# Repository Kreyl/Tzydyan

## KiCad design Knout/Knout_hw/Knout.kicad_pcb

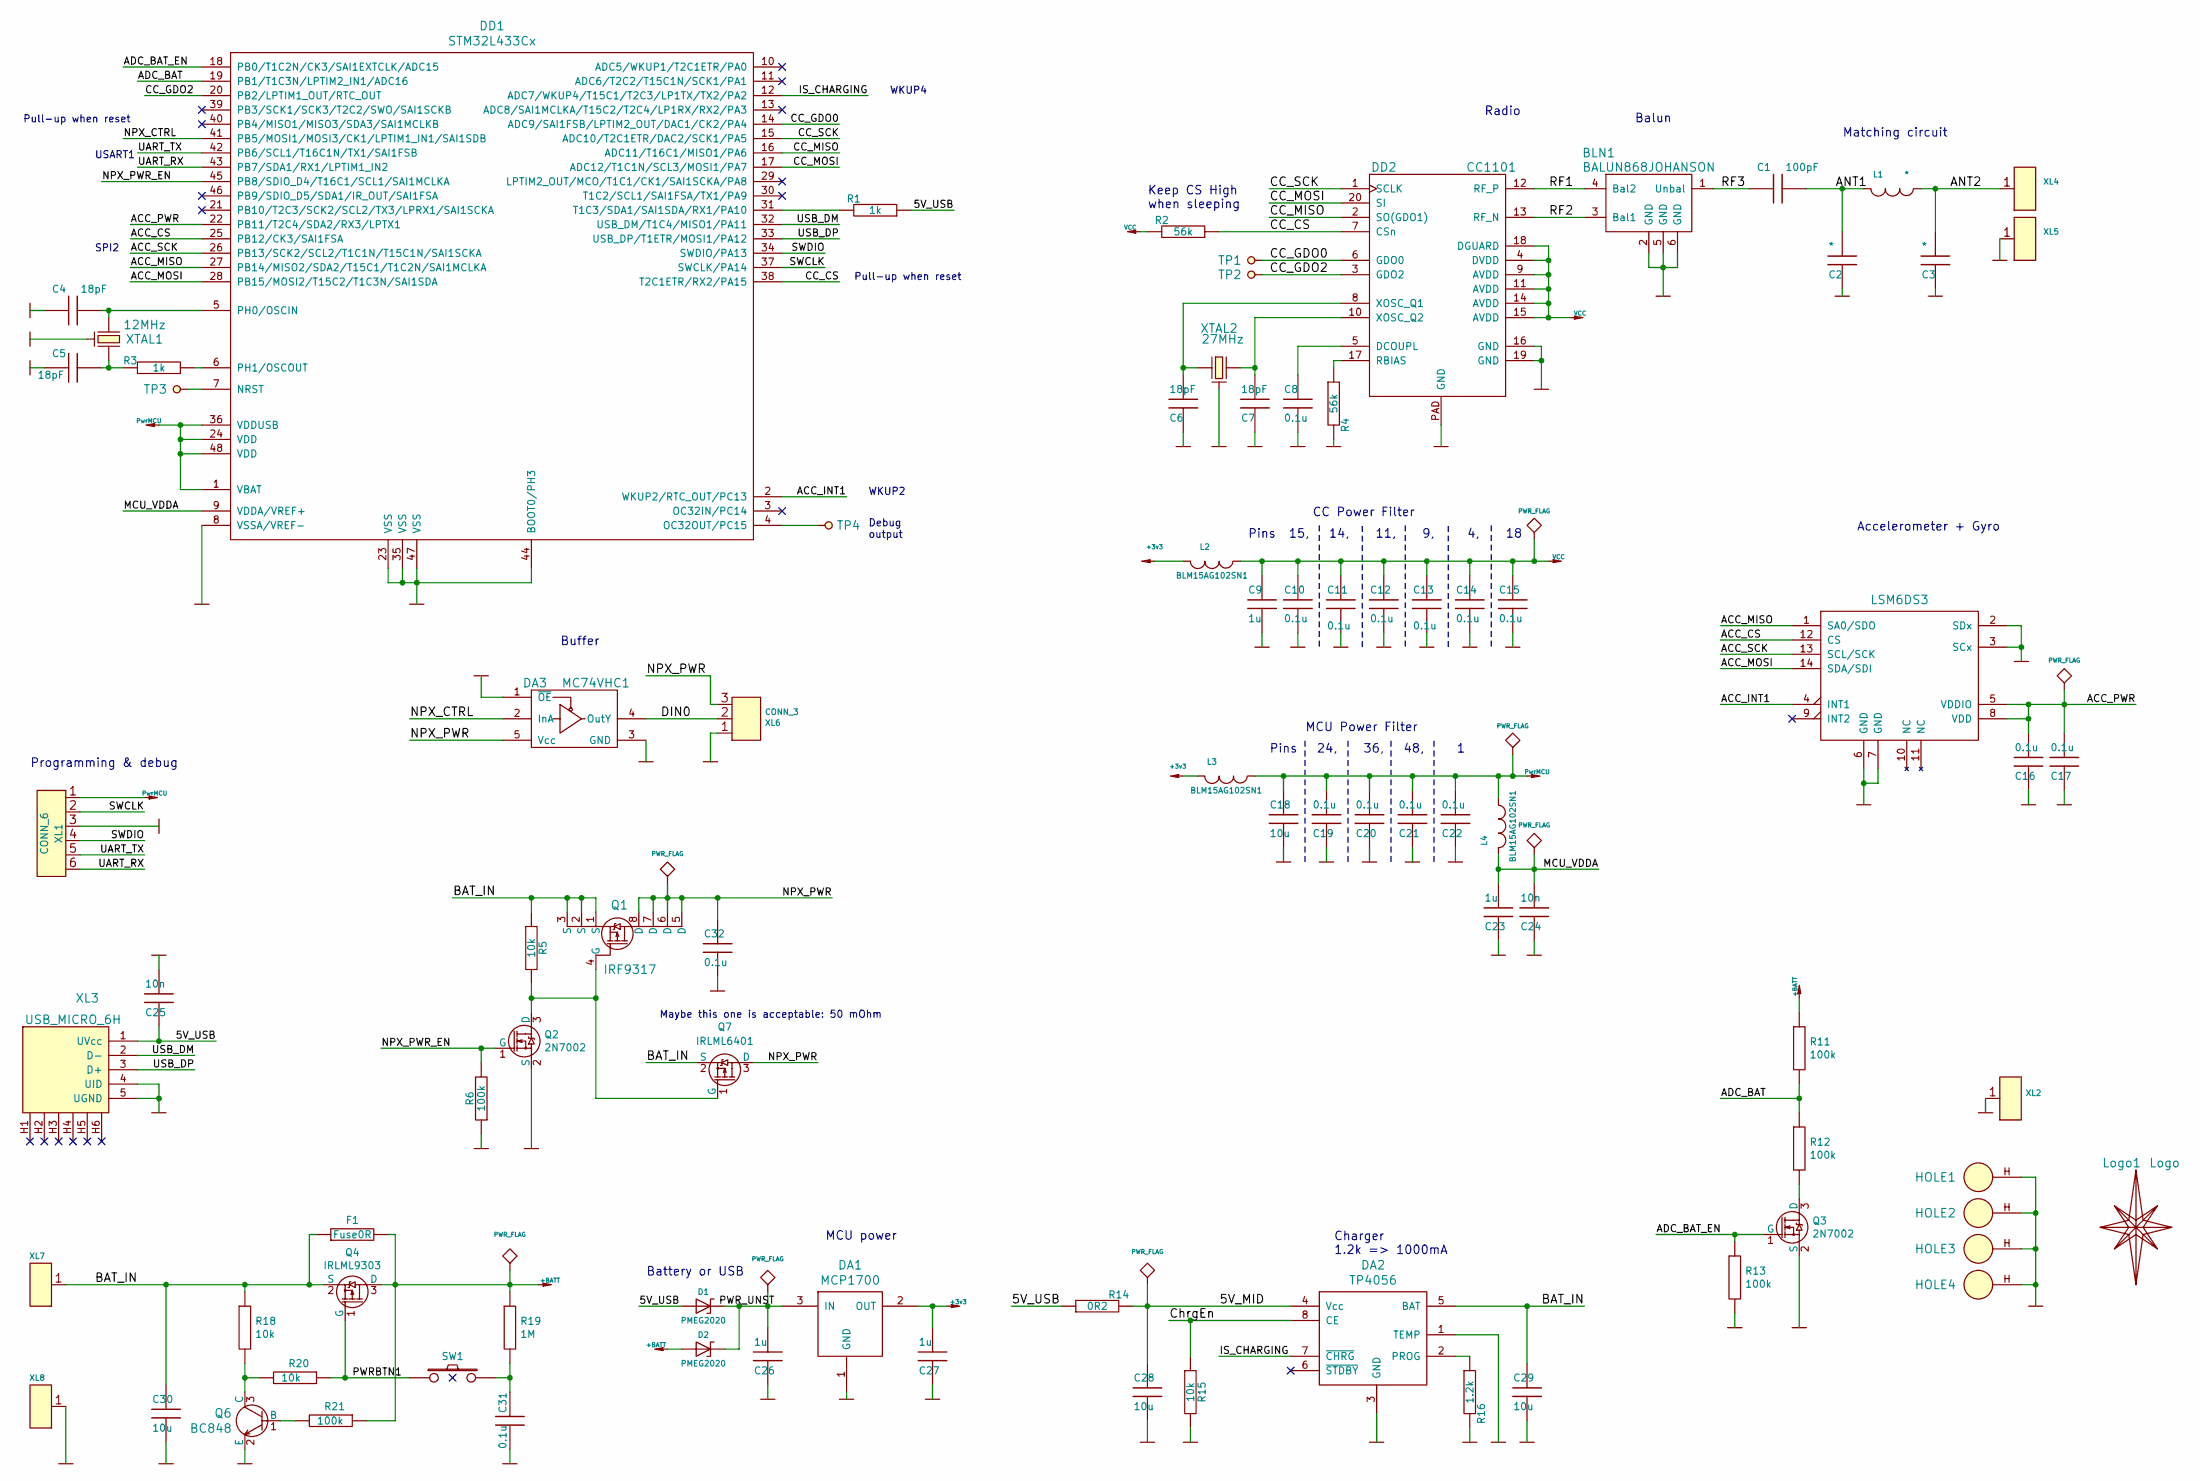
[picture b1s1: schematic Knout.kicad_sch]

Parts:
BLN1: BALUN868JOHANSON; BALUN_JOHANSON868
C1: 100pF; CAP_0402
C2, C3: *; CAP_0402
C4, C5, C6, C7: 18pF; CAP_0603_Silks
C8, C10, C11, C12, C13, C14, C15, C16, C17, C19, C20, C21, C22, C31, C32: 0.1u; CAP_0603_Silks
C9, C23, C26, C27: 1u; CAP_0603_Silks
C18, C28, C29, C30: 10u; CAP_0603_Silks
C24, C25: 10n; CAP_0603_Silks
D1, D2: PMEG2020; SOD323
DA1: MCP1700; SOT23-3A
DA2: TP4056; SO8_150MIL
DA3: MC74VHC1; SOT23-5
DD1: STM32L433Cx; LQFP48
DD2: CC1101; QFN20
DD3: LSM6DS3; 14_3x2d5_p0d5
F1: Fuse0R; RES_0603_FUSE
HOLE1, HOLE2, HOLE3, HOLE4: HOLE_METALLED; Hole2d2_out3d5mm
L1: *; IND_0402
L2, L3, L4: BLM15AG102SN1; IND_0402
Logo1: Logo; Ostranna_8x8
Q1: IRF9317; SO8_150MIL
Q2, Q3: 2N7002; SOT23-3
Q4: IRLML9303; SOT23-3
Q6: BC848; SOT23-3
Q7: IRLML6401; SOT23-3
R1, R3: 1k; RES_0603
R2, R4: 56k; RES_0603
R5, R15, R18, R20: 10k; RES_0603
R6, R11, R12, R13, R21: 100k; RES_0603
R14: 0R2; RES_1206
R16: 1.2k; RES_0603
R19: 1M; RES_0603
SW1: BUTTON_H; BTN_IT1198
TP1, TP2, TP3, TP4: TESTPOINT; TESTPOINT_1MM
XL1: CONN_6; PLS-6
XL2, XL7: CONN_1; PLS-1Rnd
XL3: USB_MICRO_6H; USBmicro_MOLEX_1050170001
XL4, XL5, XL8: CONN_1; PLS-1Square
XL6: CONN_3; SLD_3_2D5
XTAL1: 12MHz; 03225C4
XTAL2: 27MHz; 03225C4

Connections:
+3v3: C27.1, DA1.2 (OUT), L2.2, L3.2
+BATT: D2.A, F1.2, Q4.3 (D), R11.1, R19.1, R21.1
/5V_MID: C28.2, DA2.4 (Vcc), R14.2
/5V_USB: C25.2, D1.A, R1.1, R14.1, XL3.1 (UVcc)
/ACC_CS: DD1.25 (PB12/CK3/SAI1FSA), DD3.12 (CS)
/ACC_INT1: DD1.2 (WKUP2/RTC_OUT/PC13), DD3.4 (INT1)
/ACC_MISO: DD1.27 (PB14/MISO2/SDA2/T15C1/T1C2N/SAI1MCLKA), DD3.1 (SA0/SDO)
/ACC_MOSI: DD1.28 (PB15/MOSI2/T15C2/T1C3N/SAI1SDA), DD3.14 (SDA/SDI)
/ACC_PWR: C16.1, C17.1, DD1.22 (PB11/T2C4/SDA2/RX3/LPTX1), DD3.5 (VDDIO), DD3.8 (VDD)
/ACC_SCK: DD1.26 (PB13/SCK2/SCL2/T1C1N/T15C1N/SAI1SCKA), DD3.13 (SCL/SCK)
/ADC_BAT: DD1.19 (PB1/T1C3N/LPTIM2_IN1/ADC16), R11.2, R12.1
/ADC_BAT_EN: DD1.18 (PB0/T1C2N/CK3/SAI1EXTCLK/ADC15), Q3.1 (G), R13.1
/ANT1: C1.1, C2.1, L1.2
/ANT2: C3.1, L1.1, XL4.1
/BAT_IN: C29.2, C30.2, DA2.5 (BAT), F1.1, Q1.1 (S), Q1.2 (S), Q1.3 (S), Q4.2 (S), Q7.2 (S), R5.1, R18.1, XL7.1
/CC_CS: DD1.38 (T2C1ETR/RX2/PA15), DD2.7 (CSn), R2.1
/CC_GDO0: DD1.14 (ADC9/SAI1FSB/LPTIM2_OUT/DAC1/CK2/PA4), DD2.6 (GDO0), TP1.1
/CC_GDO2: DD1.20 (PB2/LPTIM1_OUT/RTC_OUT), DD2.3 (GDO2), TP2.1
/CC_MISO: DD1.16 (ADC11/T16C1/MISO1/PA6), DD2.2 (SO(GDO1))
/CC_MOSI: DD1.17 (ADC12/T1C1N/SCL3/MOSI1/PA7), DD2.20 (SI)
/CC_SCK: DD1.15 (ADC10/T2C1ETR/DAC2/SCK1/PA5), DD2.1 (SCLK)
/ChrgEn: DA2.8 (CE), R15.1
/DIN0: DA3.4 (OutY), XL6.2 (PM)
/IS_CHARGING: DA2.7 (~CHRG), DD1.12 (ADC7/WKUP4/T15C1/T2C3/LP1TX/TX2/PA2)
/MCU_VDDA: C23.1, C24.1, DD1.9 (VDDA/VREF+), L4.2
/NPX_CTRL: DA3.2 (InA), DD1.41 (PB5/MOSI1/MOSI3/CK1/LPTIM1_IN1/SAI1SDB)
/NPX_PWR: C32.2, DA3.5 (Vcc), Q1.5 (D), Q1.6 (D), Q1.7 (D), Q1.8 (D), Q7.3 (D), XL6.3
/NPX_PWR_EN: DD1.45 (PB8/SDIO_D4/T16C1/SCL1/SAI1MCLKA), Q2.1 (G), R6.2
/PWRBTN1: Q4.1 (G), R20.1, SW1.1
/PWR_UNST: C26.1, D1.C, D2.C, DA1.3 (IN)
/RF1: BLN1.4 (Bal2), DD2.12 (RF_P)
/RF2: BLN1.3 (Bal1), DD2.13 (RF_N)
/RF3: BLN1.1 (Unbal), C1.2
/SWCLK: DD1.37 (SWCLK/PA14), XL1.2
/SWDIO: DD1.34 (SWDIO/PA13), XL1.4
/UART_RX: DD1.43 (PB7/SDA1/RX1/LPTIM1_IN2), XL1.6
/UART_TX: DD1.42 (PB6/SCL1/T16C1N/TX1/SAI1FSB), XL1.5
/USB_DM: DD1.32 (USB_DM/T1C4/MISO1/PA11), XL3.2 (D-)
/USB_DP: DD1.33 (USB_DP/T1ETR/MOSI1/PA12), XL3.3 (D+)
GND: BLN1.2 (GND), BLN1.5 (GND), BLN1.6 (GND), C2.2, C3.2, C4.2, C5.2, C6.2, C7.2, C8.1, C9.2, C10.2, C11.2, C12.2, C13.2, C14.2, C15.2, C16.2, C17.2, C18.1, C19.2, C20.2, C21.2, C22.2, C23.2, C24.2, C25.1, C26.2, C27.2, C28.1, C29.1, C30.1, C31.2, C32.1, DA1.1 (GND), DA2.1 (TEMP), DA2.3 (GND), DA3.1 (~OE), DA3.3 (GND), DD1.8 (VSSA/VREF-), DD1.23 (VSS), DD1.35 (VSS), DD1.44 (BOOT0/PH3), DD1.47 (VSS), DD2.16 (GND), DD2.19 (GND), DD2.PAD (GND), DD3.2 (SDx), DD3.3 (SCx), DD3.6 (GND), DD3.7 (GND), HOLE1.H, HOLE2.H, HOLE3.H, HOLE4.H, Q2.2 (S), Q3.2 (S), Q6.2 (E), R4.2, R6.1, R13.2, R15.2, R16.2, XL1.3, XL2.1, XL3.4 (UID), XL3.5 (UGND), XL5.1, XL6.1, XL8.1, XTAL1.H, XTAL2.H
unnamed: C4.1, DD1.5 (PH0/OSCIN), XTAL1.1
unnamed: C5.1, R3.2, XTAL1.2
unnamed: C6.1, DD2.8 (XOSC_Q1), XTAL2.1
unnamed: C7.1, DD2.10 (XOSC_Q2), XTAL2.2
unnamed: C8.2, DD2.5 (DCOUPL)
unnamed: C31.1, R19.2, SW1.2
unnamed: DA2.2 (PROG), R16.1
unnamed: DD1.4 (OC32OUT/PC15), TP4.1
unnamed: DD1.6 (PH1/OSCOUT), R3.1
unnamed: DD1.7 (NRST), TP3.1
unnamed: DD1.31 (T1C3/SDA1/SAI1SDA/RX1/PA10), R1.2
unnamed: DD2.17 (RBIAS), R4.1
unnamed: Q1.4 (G), Q2.3 (D), Q7.1 (G), R5.2
unnamed: Q3.3 (D), R12.2
unnamed: Q6.1 (B), R21.2
unnamed: Q6.3 (C), R18.2, R20.2
PwrMCU: C18.2, C19.1, C20.1, C21.1, C22.1, DD1.1 (VBAT), DD1.24 (VDD), DD1.36 (VDDUSB), DD1.48 (VDD), L3.1, L4.1, XL1.1
VCC: C9.1, C10.1, C11.1, C12.1, C13.1, C14.1, C15.1, DD2.4 (DVDD), DD2.9 (AVDD), DD2.11 (AVDD), DD2.14 (AVDD), DD2.15 (AVDD), DD2.18 (DGUARD), L2.1, R2.2

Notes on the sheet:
Pull-up when reset
Programming & debug
USART1
SPI2
Buffer
Battery or USB
MCU power
WKUP2
Debug output
Maybe this one is acceptable: 50 mOhm
WKUP4
Keep CS High when sleeping
Pins 15, 14, 11, 9, 4, 18
Pins 24, 36, 48, 1
MCU Power Filter
CC Power Filter
Charger 1.2k => 1000mA
Radio
Balun
Matching circuit
Accelerometer + Gyro

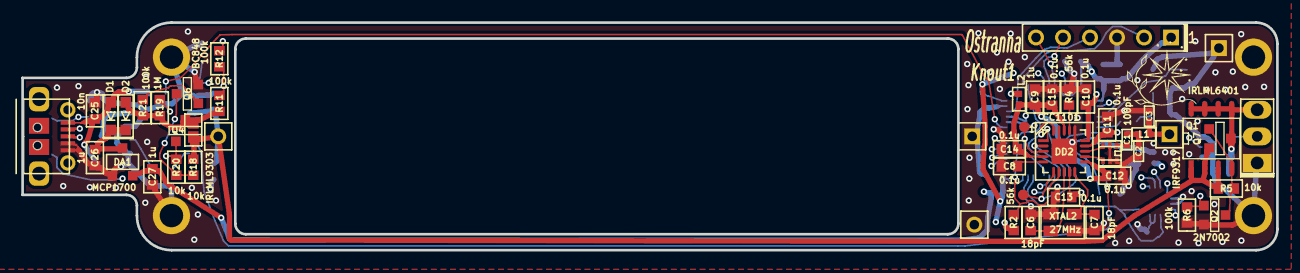
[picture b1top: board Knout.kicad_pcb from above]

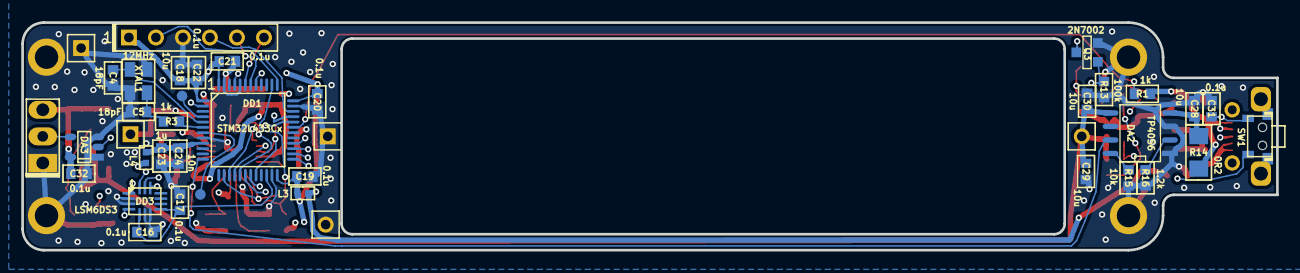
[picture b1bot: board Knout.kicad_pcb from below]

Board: 4 copper layers, 118.0 x 21.4 mm, 88 parts (33 on the bottom side), 58 nets.

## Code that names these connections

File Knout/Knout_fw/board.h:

#pragma once

// ==== General ====
#define APP_NAME                "Knout"

// Version of PCB
#define PCB_VER                 1

// MCU type as defined in the ST header.
#define STM32L433xx

// Freq of external crystal if any. Leave it here even if not used.
#define CRYSTAL_FREQ_HZ         12000000

// OS timer settings
#define STM32_ST_IRQ_PRIORITY   2
#define STM32_ST_USE_TIMER      2
#define SYS_TIM_CLK             (Clk.APB1FreqHz)    // Timer 5 is clocked by APB1

//  Periphery
#define I2C1_ENABLED            FALSE
#define I2C2_ENABLED            FALSE
#define I2C3_ENABLED            FALSE
#define SIMPLESENSORS_ENABLED   FALSE
#define BUTTONS_ENABLED         FALSE

#define ADC_REQUIRED            FALSE
#define STM32_DMA_REQUIRED      TRUE    // Leave this macro name for OS

#if 1 // ========================== GPIO =======================================
// EXTI
#define INDIVIDUAL_EXTI_IRQ_REQUIRED    FALSE

// Battery
#define IS_CHARGING     GPIOA, 2
#define BAT_MEAS_EN     GPIOB, 0
#define BAT_ADC_PIN     GPIOB, 1

// USB
#define USB_DM          GPIOA, 11
#define USB_DP          GPIOA, 12
#define USB_AF          AF10
#define USB_DETECT_PIN  GPIOA, 10

// Radio: SPI, PGpio, Sck, Miso, Mosi, Cs, Gdo0
#define CC_Setup0       SPI1, GPIOA, 5,6,7, GPIOA,15, GPIOA,4

// UART
#define UART_GPIO       GPIOB
#define UART_TX_PIN     6
#define UART_RX_PIN     7

// Acc
#define ACG_IRQ_PIN     GPIOC, 13
#define ACG_CS_PIN      GPIOB, 12
#define ACG_SCK_PIN     GPIOB, 13, omPushPull, pudNone, AF5
#define ACG_MISO_PIN    GPIOB, 14, omPushPull, pudNone, AF5
#define ACG_MOSI_PIN    GPIOB, 15, omPushPull, pudNone, AF5
#define ACG_PWR_PIN     GPIOB, 11
#define ACG_SPI         SPI2

// Npx LEDs
#define NPX_CNT         176 // Used in Effects
#define NPX_PER_BAND    (NPX_CNT/2)
#define NPX_SPI         SPI3
#define NPX_DATA_PIN    GPIOB, 5, AF6
#define NPX_PWR_PIN     GPIOB, 8

#endif // GPIO

#if ADC_REQUIRED // ======================= Inner ADC ==========================
// Clock divider: clock is generated from the APB2
#define ADC_CLK_DIVIDER		adcDiv2

// ADC channels
#define ADC_BATTERY_CHNL 	14
// ADC_VREFINT_CHNL
#define ADC_CHANNELS        { ADC_BATTERY_CHNL, ADC_VREFINT_CHNL }
#define ADC_CHANNEL_CNT     2   // Do not use countof(AdcChannels) as preprocessor does not know what is countof => cannot check
#define ADC_SAMPLE_TIME     ast24d5Cycles
#define ADC_OVERSAMPLING_RATIO  64   // 1 (no oversampling), 2, 4, 8, 16, 32, 64, 128, 256
#endif

#if 1 // =========================== DMA =======================================
// ==== Uart ====
// Remap is made automatically if required
#define UART_DMA_TX     STM32_DMA_STREAM_ID(2, 6)
#define UART_DMA_RX     STM32_DMA_STREAM_ID(2, 7)
#define UART_DMA_CHNL   2
#define UART_DMA_TX_MODE(Chnl) (STM32_DMA_CR_CHSEL(Chnl) | DMA_PRIORITY_LOW | STM32_DMA_CR_MSIZE_BYTE | STM32_DMA_CR_PSIZE_BYTE | STM32_DMA_CR_MINC | STM32_DMA_CR_DIR_M2P | STM32_DMA_CR_TCIE)
#define UART_DMA_RX_MODE(Chnl) (STM32_DMA_CR_CHSEL(Chnl) | DMA_PRIORITY_MEDIUM | STM32_DMA_CR_MSIZE_BYTE | STM32_DMA_CR_PSIZE_BYTE | STM32_DMA_CR_MINC | STM32_DMA_CR_DIR_P2M | STM32_DMA_CR_CIRC)

#define NPX_DMA         STM32_DMA_STREAM_ID(2, 2)  // SPI3 TX
#define NPX_DMA_CHNL    3

// ==== ACG ====
#define ACG_DMA_TX      STM32_DMA_STREAM_ID(1, 5)
#define ACG_DMA_RX      STM32_DMA_STREAM_ID(1, 4)
#define ACG_DMA_CHNL    1

#if ADC_REQUIRED
#define ADC_DMA         STM32_DMA1_STREAM1
#define ADC_DMA_MODE    STM32_DMA_CR_CHSEL(0) |   /* DMA1 Stream1 Channel0 */ \
                        DMA_PRIORITY_LOW | \
                        STM32_DMA_CR_MSIZE_HWORD | \
                        STM32_DMA_CR_PSIZE_HWORD | \
                        STM32_DMA_CR_MINC |       /* Memory pointer increase */ \
                        STM32_DMA_CR_DIR_P2M |    /* Direction is peripheral to memory */ \
                        STM32_DMA_CR_TCIE         /* Enable Transmission Complete IRQ */
#endif // ADC

#endif // DMA

#if 1 // ========================== USART ======================================
#define PRINTF_FLOAT_EN FALSE
#define UART_TXBUF_SZ   2048
#define UART_RXBUF_SZ   99

#define UARTS_CNT       1

#define CMD_UART_PARAMS \
    USART1, UART_GPIO, UART_TX_PIN, UART_GPIO, UART_RX_PIN, \
    UART_DMA_TX, UART_DMA_RX, UART_DMA_TX_MODE(UART_DMA_CHNL), UART_DMA_RX_MODE(UART_DMA_CHNL), \
    true // Use independent clock

#endif

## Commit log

2021-01-16 Snake sch seems done
2021-01-27 + Snake layout done
2021-01-31 + Snake sent to production + Knout layout done
2021-02-07 + Snake fw started
2021-02-14 + Radio works + Knout effects work
